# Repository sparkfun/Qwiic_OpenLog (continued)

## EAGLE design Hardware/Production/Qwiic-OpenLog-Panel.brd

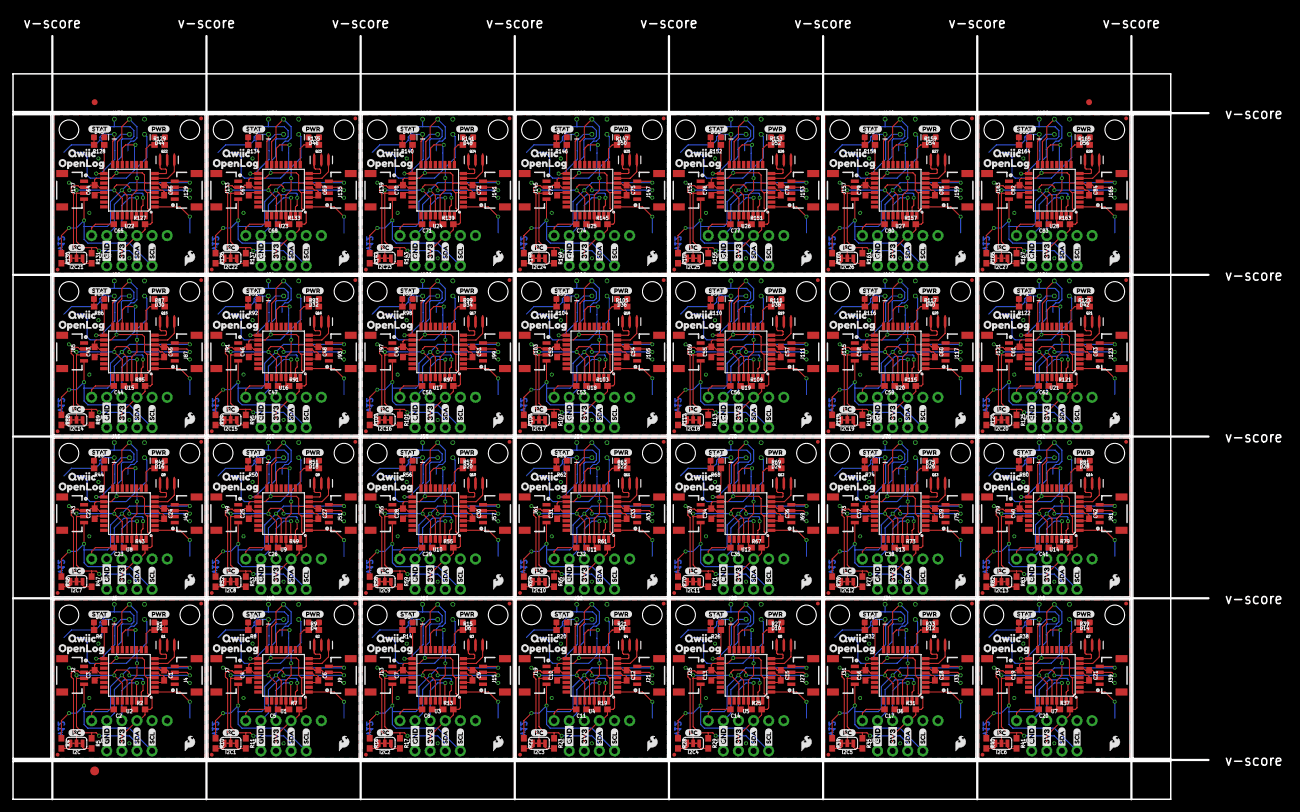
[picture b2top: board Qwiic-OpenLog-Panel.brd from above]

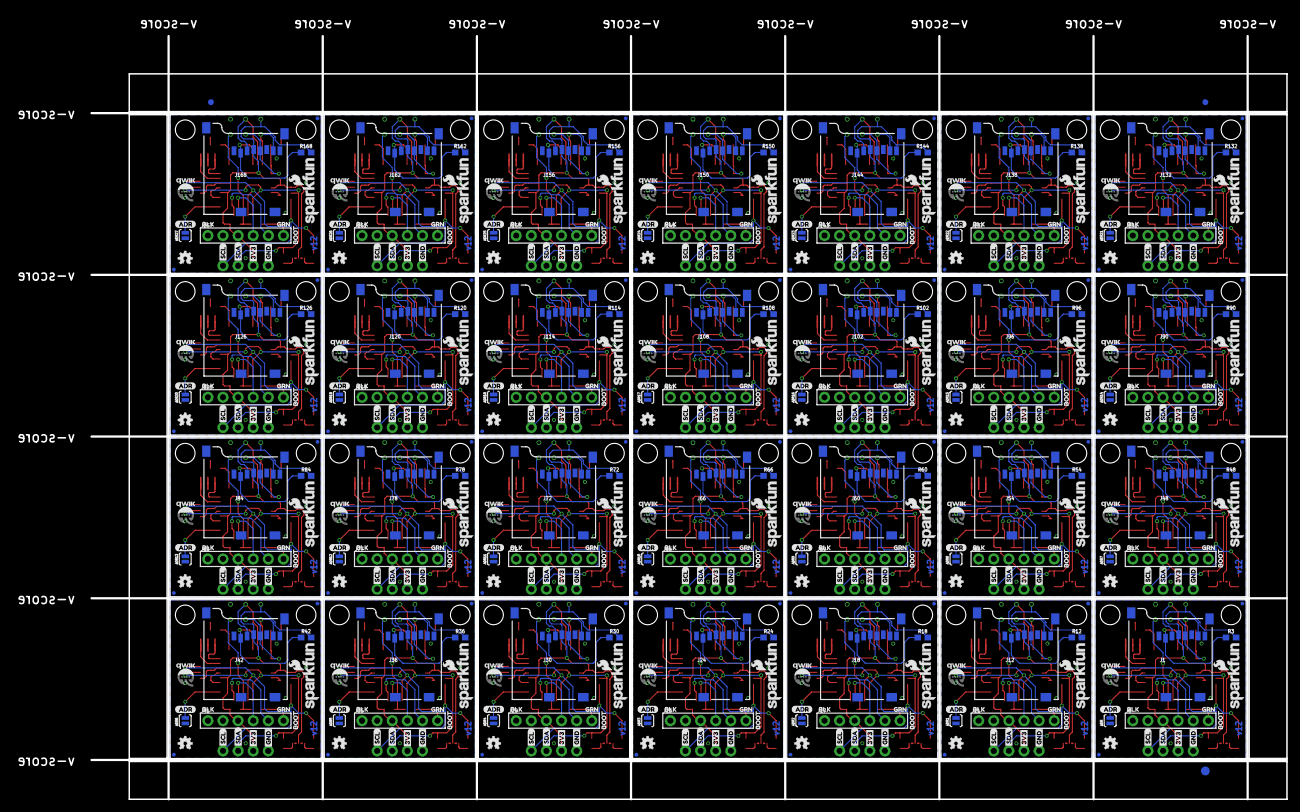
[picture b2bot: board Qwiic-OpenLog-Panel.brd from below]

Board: 2 copper layers, 200.9 x 128.3 mm, 1350 parts (479 on the bottom side), 560 nets.

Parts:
ADR, ADR1, ADR2, ADR3, ADR4, ADR5, ADR6, ADR7, ADR8, ADR9, ADR10, ADR11, ADR12, ADR13, ADR14, ADR15, ADR16, ADR17, ADR18, ADR19, ADR20, ADR21, ADR22, ADR23, ADR24, ADR25, ADR26, ADR27: SJ_2S-NO
C1, C6, C9, C12, C15, C18, C21, C24, C27, C30, C33, C36, C39, C42, C45, C48, C51, C54, C57, C60, C63, C66, C69, C72, C75, C78, C81, C84: 4.7uF; 0603
C2, C3, C4, C5, C7, C8, C10, C11, C13, C14, C16, C17, C19, C20, C22, C23, C25, C26, C28, C29, C31, C32, C34, C35, C37, C38, C40, C41, C43, C44, C46, C47, C49, C50, C52, C53, C55, C56, C58, C59, C61, C62, C64, C65, C67, C68, C70, C71, C73, C74, C76, C77, C79, C80, C82, C83: 0.1uF; 0603
D1, D4, D6, D8, D10, D12, D14, D16, D18, D20, D22, D24, D26, D28, D30, D32, D34, D36, D38, D40, D42, D44, D46, D48, D50, D52, D54, D56: RED; LED-0603
D2, D3, D5, D7, D9, D11, D13, D15, D17, D19, D21, D23, D25, D27, D29, D31, D33, D35, D37, D39, D41, D43, D45, D47, D49, D51, D53, D55: GREEN; LED-0603
E$1, E$2, E$3, E$4: FIDUCIAL-1X2
E$5, E$6: FIDUCIAL-1.5X3
FID1, FID2, FID3, FID4, FID5, FID6, FID7, FID8, FID9, FID10, FID11, FID12, FID13, FID14, FID15, FID16, FID17, FID18, FID19, FID20, FID21, FID22, FID23, FID24, FID25, FID26, FID27, FID28, FID29, FID30, FID31, FID32, FID33, FID34, FID35, FID36, FID37, FID38, FID39, FID40, FID41, FID42, FID43, FID44, FID45, FID46, FID47, FID48, FID49, FID50, FID51, FID52, FID53, FID54, FID55, FID56, FID57, FID58, FID59, FID60, FID61, FID62, FID63, FID64, FID65, FID66, FID67, FID68, FID69, FID70, FID71, FID72, FID73, FID74, FID75, FID76, FID77, FID78, FID79, FID80, FID81, FID82, FID83, FID84, FID85, FID86, FID87, FID88, FID89, FID90, FID91, FID92, FID93, FID94, FID95, FID96, FID97, FID98, FID99, FID100, FID101, FID102, FID103, FID104, FID105, FID106, FID107, FID108, FID109, FID110, FID111, FID112: FIDUCIALUFIDUCIAL; FIDUCIAL-MICRO
I2C, I2C1, I2C2, I2C3, I2C4, I2C5, I2C6, I2C7, I2C8, I2C9, I2C10, I2C11, I2C12, I2C13, I2C14, I2C15, I2C16, I2C17, I2C18, I2C19, I2C20, I2C21, I2C22, I2C23, I2C24, I2C25, I2C26, I2C27: SMT-JUMPER_3_2-NC_TRACE_SILK
J1, J12, J18, J24, J30, J36, J42, J48, J54, J60, J66, J72, J78, J84, J90, J96, J102, J108, J114, J120, J126, J132, J138, J144, J150, J156, J162, J168: MICRO-SD; MICRO-SD-SOCKET
J2, J4, J7, J9, J13, J15, J19, J21, J25, J27, J31, J33, J37, J39, J43, J45, J49, J51, J55, J57, J61, J63, J67, J69, J73, J75, J79, J81, J85, J87, J91, J93, J97, J99, J103, J105, J109, J111, J115, J117, J121, J123, J127, J129, J133, J135, J139, J141, J145, J147, J151, J153, J157, J159, J163, J165: SMD; 1X04_1MM_RA
J3, J8, J14, J20, J26, J32, J38, J44, J50, J56, J62, J68, J74, J80, J86, J92, J98, J104, J110, J116, J122, J128, J134, J140, J146, J152, J158, J164: PTH; 1X04_NO_SILK
J5, J10, J16, J22, J28, J34, J40, J46, J52, J58, J64, J70, J76, J82, J88, J94, J100, J106, J112, J118, J124, J130, J136, J142, J148, J154, J160, J166: ISP; 2X3_TEST_POINTS
J6, J11, J17, J23, J29, J35, J41, J47, J53, J59, J65, J71, J77, J83, J89, J95, J101, J107, J113, J119, J125, J131, J137, J143, J149, J155, J161, J167: 1X06_NO_SILK
JP1, JP2, JP3, JP4, JP5, JP6, JP7, JP8, JP9, JP10, JP11, JP12, JP13, JP14, JP15, JP16, JP17, JP18, JP19, JP20, JP21, JP22, JP23, JP24, JP25, JP26, JP27, JP28, JP29, JP30, JP31, JP32, JP33, JP34, JP35, JP36, JP37, JP38, JP39, JP40, JP41, JP42, JP43, JP44, JP45, JP46, JP47, JP48, JP49, JP50, JP51, JP52, JP53, JP54, JP55, JP56: STAND-OFF
LOGO1, LOGO6, LOGO9, LOGO12, LOGO15, LOGO18, LOGO21, LOGO24, LOGO27, LOGO30, LOGO33, LOGO36, LOGO39, LOGO42, LOGO45, LOGO48, LOGO51, LOGO54, LOGO57, LOGO60, LOGO63, LOGO66, LOGO69, LOGO72, LOGO75, LOGO78, LOGO81, LOGO84: SFE_LOGO_FLAME.1_INCH; SFE_LOGO_FLAME_.1
LOGO2, LOGO3, LOGO7, LOGO10, LOGO13, LOGO16, LOGO19, LOGO22, LOGO25, LOGO28, LOGO31, LOGO34, LOGO37, LOGO40, LOGO43, LOGO46, LOGO49, LOGO52, LOGO55, LOGO58, LOGO61, LOGO64, LOGO67, LOGO70, LOGO73, LOGO76, LOGO79, LOGO82: OSHW-LOGOMINI; OSHW-LOGO-MINI
LOGO4, LOGO5, LOGO8, LOGO11, LOGO14, LOGO17, LOGO20, LOGO23, LOGO26, LOGO29, LOGO32, LOGO35, LOGO38, LOGO41, LOGO44, LOGO47, LOGO50, LOGO53, LOGO56, LOGO59, LOGO62, LOGO65, LOGO68, LOGO71, LOGO74, LOGO77, LOGO80, LOGO83: SFE_LOGO_NAME_FLAME.1_INCH; SFE_LOGO_NAME_FLAME_.1
Q1, Q2, Q3, Q4, Q5, Q6, Q7, Q8, Q9, Q10, Q11, Q12, Q13, Q14, Q15, Q16, Q17, Q18, Q19, Q20, Q21, Q22, Q23, Q24, Q25, Q26, Q27, Q28: 16MHZ; RESONATOR-SMD
R1, R9, R15, R21, R27, R33, R39, R45, R51, R57, R63, R69, R75, R81, R87, R93, R99, R105, R111, R117, R123, R129, R135, R141, R147, R153, R159, R165: 1k; 0603
R2, R3, R7, R12, R13, R18, R19, R24, R25, R30, R31, R36, R37, R42, R43, R48, R49, R54, R55, R60, R61, R66, R67, R72, R73, R78, R79, R84, R85, R90, R91, R96, R97, R102, R103, R108, R109, R114, R115, R120, R121, R126, R127, R132, R133, R138, R139, R144, R145, R150, R151, R156, R157, R162, R163, R168: 10k; 0603
R4, R5, R10, R11, R16, R17, R22, R23, R28, R29, R34, R35, R40, R41, R46, R47, R52, R53, R58, R59, R64, R65, R70, R71, R76, R77, R82, R83, R88, R89, R94, R95, R100, R101, R106, R107, R112, R113, R118, R119, R124, R125, R130, R131, R136, R137, R142, R143, R148, R149, R154, R155, R160, R161, R166, R167: 2.2k; 0603
R6, R8, R14, R20, R26, R32, R38, R44, R50, R56, R62, R68, R74, R80, R86, R92, R98, R104, R110, R116, R122, R128, R134, R140, R146, R152, R158, R164: 330; 0603
U1, U2, U3, U4, U5, U6, U7, U8, U9, U10, U11, U12, U13, U14, U15, U16, U17, U18, U19, U20, U21, U22, U23, U24, U25, U26, U27, U28: ATMEGA328P; TQFP32-08
U$1, U$4, U$37, U$55, U$73, U$91, U$109, U$127, U$145, U$163, U$181, U$199, U$217, U$235, U$253, U$271, U$289, U$307, U$325, U$343, U$361, U$379, U$397, U$415, U$433, U$451, U$469, U$487: 3V3-03
U$2, U$5, U$38, U$56, U$74, U$92, U$110, U$128, U$146, U$164, U$182, U$200, U$218, U$236, U$254, U$272, U$290, U$308, U$326, U$344, U$362, U$380, U$398, U$416, U$434, U$452, U$470, U$488: GND-03
U$3, U$36, U$54, U$72, U$90, U$108, U$126, U$144, U$162, U$180, U$198, U$216, U$234, U$252, U$270, U$288, U$306, U$324, U$342, U$360, U$378, U$396, U$414, U$432, U$450, U$468, U$486, U$504: QWIIC-LOGO-SMALL
U$6, U$34, U$52, U$70, U$88, U$106, U$124, U$142, U$160, U$178, U$196, U$214, U$232, U$250, U$268, U$286, U$304, U$322, U$340, U$358, U$376, U$394, U$412, U$430, U$448, U$466, U$484, U$502: 3V30
U$7, U$21, U$39, U$57, U$75, U$93, U$111, U$129, U$147, U$165, U$183, U$201, U$219, U$237, U$255, U$273, U$291, U$309, U$327, U$345, U$363, U$381, U$399, U$417, U$435, U$453, U$471, U$489: ADR-()-03
U$8, U$22, U$40, U$58, U$76, U$94, U$112, U$130, U$148, U$166, U$184, U$202, U$220, U$238, U$256, U$274, U$292, U$310, U$328, U$346, U$364, U$382, U$400, U$418, U$436, U$454, U$472, U$490: I_SUPER2_C-()-03
U$9, U$23, U$41, U$59, U$77, U$95, U$113, U$131, U$149, U$167, U$185, U$203, U$221, U$239, U$257, U$275, U$293, U$311, U$329, U$347, U$365, U$383, U$401, U$419, U$437, U$455, U$473, U$491: PWR-()-03
U$10, U$24, U$42, U$60, U$78, U$96, U$114, U$132, U$150, U$168, U$186, U$204, U$222, U$240, U$258, U$276, U$294, U$312, U$330, U$348, U$366, U$384, U$402, U$420, U$438, U$456, U$474, U$492: BLK3
U$11, U$25, U$43, U$61, U$79, U$97, U$115, U$133, U$151, U$169, U$187, U$205, U$223, U$241, U$259, U$277, U$295, U$313, U$331, U$349, U$367, U$385, U$403, U$421, U$439, U$457, U$475, U$493: BOOT5
U$12, U$26, U$44, U$62, U$80, U$98, U$116, U$134, U$152, U$170, U$188, U$206, U$224, U$242, U$260, U$278, U$296, U$314, U$332, U$350, U$368, U$386, U$404, U$422, U$440, U$458, U$476, U$494: GRN4
U$13, U$16, U$29, U$32, U$47, U$50, U$65, U$68, U$83, U$86, U$101, U$104, U$119, U$122, U$137, U$140, U$155, U$158, U$173, U$176, U$191, U$194, U$209, U$212, U$227, U$230, U$245, U$248, U$263, U$266, U$281, U$284, U$299, U$302, U$317, U$320, U$335, U$338, U$353, U$356, U$371, U$374, U$389, U$392, U$407, U$410, U$425, U$428, U$443, U$446, U$461, U$464, U$479, U$482, U$497, U$500: SDA1
U$14, U$27, U$45, U$63, U$81, U$99, U$117, U$135, U$153, U$171, U$189, U$207, U$225, U$243, U$261, U$279, U$297, U$315, U$333, U$351, U$369, U$387, U$405, U$423, U$441, U$459, U$477, U$495: QWIIC7
U$15, U$19, U$28, U$33, U$46, U$51, U$64, U$69, U$82, U$87, U$100, U$105, U$118, U$123, U$136, U$141, U$154, U$159, U$172, U$177, U$190, U$195, U$208, U$213, U$226, U$231, U$244, U$249, U$262, U$267, U$280, U$285, U$298, U$303, U$316, U$321, U$334, U$339, U$352, U$357, U$370, U$375, U$388, U$393, U$406, U$411, U$424, U$429, U$442, U$447, U$460, U$465, U$478, U$483, U$496, U$501: SCL2
U$17, U$30, U$48, U$66, U$84, U$102, U$120, U$138, U$156, U$174, U$192, U$210, U$228, U$246, U$264, U$282, U$300, U$318, U$336, U$354, U$372, U$390, U$408, U$426, U$444, U$462, U$480, U$498: STAT0
U$18, U$31, U$49, U$67, U$85, U$103, U$121, U$139, U$157, U$175, U$193, U$211, U$229, U$247, U$265, U$283, U$301, U$319, U$337, U$355, U$373, U$391, U$409, U$427, U$445, U$463, U$481, U$499: OPENLOG0
U$20, U$35, U$53, U$71, U$89, U$107, U$125, U$143, U$161, U$179, U$197, U$215, U$233, U$251, U$269, U$287, U$305, U$323, U$341, U$359, U$377, U$395, U$413, U$431, U$449, U$467, U$485, U$503: GND1

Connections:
3.3V: C1.1, C3.2, I2C.2, J1.VCC, J2.2, J3.2, J4.2, J5.2, J6.3, R2.2, R3.2, U2.4, U2.6, U2.18, U2.20
3.3V1: C4.2, C6.1, I2C1.2, J7.2, J8.2, J9.2, J10.2, J11.3, J12.VCC, R7.2, R12.2, U1.4, U1.6, U1.18, U1.20
3.3V2: C7.2, C9.1, I2C2.2, J13.2, J14.2, J15.2, J16.2, J17.3, J18.VCC, R13.2, R18.2, U3.4, U3.6, U3.18, U3.20
3.3V3: C10.2, C12.1, I2C3.2, J19.2, J20.2, J21.2, J22.2, J23.3, J24.VCC, R19.2, R24.2, U4.4, U4.6, U4.18, U4.20
3.3V4: C13.2, C15.1, I2C4.2, J25.2, J26.2, J27.2, J28.2, J29.3, J30.VCC, R25.2, R30.2, U5.4, U5.6, U5.18, U5.20
3.3V5: C16.2, C18.1, I2C5.2, J31.2, J32.2, J33.2, J34.2, J35.3, J36.VCC, R31.2, R36.2, U6.4, U6.6, U6.18, U6.20
3.3V6: C19.2, C21.1, I2C6.2, J37.2, J38.2, J39.2, J40.2, J41.3, J42.VCC, R37.2, R42.2, U7.4, U7.6, U7.18, U7.20
3.3V7: C22.2, C24.1, I2C7.2, J43.2, J44.2, J45.2, J46.2, J47.3, J48.VCC, R43.2, R48.2, U8.4, U8.6, U8.18, U8.20
3.3V8: C25.2, C27.1, I2C8.2, J49.2, J50.2, J51.2, J52.2, J53.3, J54.VCC, R49.2, R54.2, U9.4, U9.6, U9.18, U9.20
3.3V9: C28.2, C30.1, I2C9.2, J55.2, J56.2, J57.2, J58.2, J59.3, J60.VCC, R55.2, R60.2, U10.4, U10.6, U10.18, U10.20
3.3V10: C31.2, C33.1, I2C10.2, J61.2, J62.2, J63.2, J64.2, J65.3, J66.VCC, R61.2, R66.2, U11.4, U11.6, U11.18, U11.20
3.3V11: C34.2, C36.1, I2C11.2, J67.2, J68.2, J69.2, J70.2, J71.3, J72.VCC, R67.2, R72.2, U12.4, U12.6, U12.18, U12.20
3.3V12: C37.2, C39.1, I2C12.2, J73.2, J74.2, J75.2, J76.2, J77.3, J78.VCC, R73.2, R78.2, U13.4, U13.6, U13.18, U13.20
3.3V13: C40.2, C42.1, I2C13.2, J79.2, J80.2, J81.2, J82.2, J83.3, J84.VCC, R79.2, R84.2, U14.4, U14.6, U14.18, U14.20
3.3V14: C43.2, C45.1, I2C14.2, J85.2, J86.2, J87.2, J88.2, J89.3, J90.VCC, R85.2, R90.2, U15.4, U15.6, U15.18, U15.20
3.3V15: C46.2, C48.1, I2C15.2, J91.2, J92.2, J93.2, J94.2, J95.3, J96.VCC, R91.2, R96.2, U16.4, U16.6, U16.18, U16.20
3.3V16: C49.2, C51.1, I2C16.2, J97.2, J98.2, J99.2, J100.2, J101.3, J102.VCC, R97.2, R102.2, U17.4, U17.6, U17.18, U17.20
3.3V17: C52.2, C54.1, I2C17.2, J103.2, J104.2, J105.2, J106.2, J107.3, J108.VCC, R103.2, R108.2, U18.4, U18.6, U18.18, U18.20
3.3V18: C55.2, C57.1, I2C18.2, J109.2, J110.2, J111.2, J112.2, J113.3, J114.VCC, R109.2, R114.2, U19.4, U19.6, U19.18, U19.20
3.3V19: C58.2, C60.1, I2C19.2, J115.2, J116.2, J117.2, J118.2, J119.3, J120.VCC, R115.2, R120.2, U20.4, U20.6, U20.18, U20.20
3.3V20: C61.2, C63.1, I2C20.2, J121.2, J122.2, J123.2, J124.2, J125.3, J126.VCC, R121.2, R126.2, U21.4, U21.6, U21.18, U21.20
3.3V21: C64.2, C66.1, I2C21.2, J127.2, J128.2, J129.2, J130.2, J131.3, J132.VCC, R127.2, R132.2, U22.4, U22.6, U22.18, U22.20
3.3V22: C67.2, C69.1, I2C22.2, J133.2, J134.2, J135.2, J136.2, J137.3, J138.VCC, R133.2, R138.2, U23.4, U23.6, U23.18, U23.20
3.3V23: C70.2, C72.1, I2C23.2, J139.2, J140.2, J141.2, J142.2, J143.3, J144.VCC, R139.2, R144.2, U24.4, U24.6, U24.18, U24.20
3.3V24: C73.2, C75.1, I2C24.2, J145.2, J146.2, J147.2, J148.2, J149.3, J150.VCC, R145.2, R150.2, U25.4, U25.6, U25.18, U25.20
3.3V25: C76.2, C78.1, I2C25.2, J151.2, J152.2, J153.2, J154.2, J155.3, J156.VCC, R151.2, R156.2, U26.4, U26.6, U26.18, U26.20
3.3V26: C79.2, C81.1, I2C26.2, J157.2, J158.2, J159.2, J160.2, J161.3, J162.VCC, R157.2, R162.2, U27.4, U27.6, U27.18, U27.20
3.3V27: C82.2, C84.1, I2C27.2, J163.2, J164.2, J165.2, J166.2, J167.3, J168.VCC, R163.2, R168.2, U28.4, U28.6, U28.18, U28.20
ADDR: ADR.2, U2.1
ADDR1: ADR1.2, U1.1
ADDR2: ADR2.2, U3.1
ADDR3: ADR3.2, U4.1
ADDR4: ADR4.2, U5.1
ADDR5: ADR5.2, U6.1
ADDR6: ADR6.2, U7.1
ADDR7: ADR7.2, U8.1
ADDR8: ADR8.2, U9.1
ADDR9: ADR9.2, U10.1
ADDR10: ADR10.2, U11.1
ADDR11: ADR11.2, U12.1
ADDR12: ADR12.2, U13.1
ADDR13: ADR13.2, U14.1
ADDR14: ADR14.2, U15.1
ADDR15: ADR15.2, U16.1
ADDR16: ADR16.2, U17.1
ADDR17: ADR17.2, U18.1
ADDR18: ADR18.2, U19.1
ADDR19: ADR19.2, U20.1
ADDR20: ADR20.2, U21.1
ADDR21: ADR21.2, U22.1
ADDR22: ADR22.2, U23.1
ADDR23: ADR23.2, U24.1
ADDR24: ADR24.2, U25.1
ADDR25: ADR25.2, U26.1
ADDR26: ADR26.2, U27.1
ADDR27: ADR27.2, U28.1
CS: J1.CS, R3.1, U2.14
CS1: J12.CS, R12.1, U1.14
CS2: J18.CS, R18.1, U3.14
CS3: J24.CS, R24.1, U4.14
CS4: J30.CS, R30.1, U5.14
CS5: J36.CS, R36.1, U6.14
CS6: J42.CS, R42.1, U7.14
CS7: J48.CS, R48.1, U8.14
CS8: J54.CS, R54.1, U9.14
CS9: J60.CS, R60.1, U10.14
CS10: J66.CS, R66.1, U11.14
CS11: J72.CS, R72.1, U12.14
CS12: J78.CS, R78.1, U13.14
CS13: J84.CS, R84.1, U14.14
CS14: J90.CS, R90.1, U15.14
CS15: J96.CS, R96.1, U16.14
CS16: J102.CS, R102.1, U17.14
CS17: J108.CS, R108.1, U18.14
CS18: J114.CS, R114.1, U19.14
CS19: J120.CS, R120.1, U20.14
CS20: J126.CS, R126.1, U21.14
CS21: J132.CS, R132.1, U22.14
CS22: J138.CS, R138.1, U23.14
CS23: J144.CS, R144.1, U24.14
CS24: J150.CS, R150.1, U25.14
CS25: J156.CS, R156.1, U26.14
CS26: J162.CS, R162.1, U27.14
CS27: J168.CS, R168.1, U28.14
DTR: C2.2, J6.6
DTR1: C5.2, J11.6
DTR2: C8.2, J17.6
DTR3: C11.2, J23.6
DTR4: C14.2, J29.6
DTR5: C17.2, J35.6
DTR6: C20.2, J41.6
DTR7: C23.2, J47.6
DTR8: C26.2, J53.6
DTR9: C29.2, J59.6
DTR10: C32.2, J65.6
DTR11: C35.2, J71.6
DTR12: C38.2, J77.6
DTR13: C41.2, J83.6
DTR14: C44.2, J89.6
DTR15: C47.2, J95.6
DTR16: C50.2, J101.6
DTR17: C53.2, J107.6
DTR18: C56.2, J113.6
DTR19: C59.2, J119.6
DTR20: C62.2, J125.6
DTR21: C65.2, J131.6
DTR22: C68.2, J137.6
DTR23: C71.2, J143.6
DTR24: C74.2, J149.6
DTR25: C77.2, J155.6
DTR26: C80.2, J161.6
DTR27: C83.2, J167.6
GND: ADR.1, C1.2, C3.1, D1.C, D3.C, J1.GND, J2.1, J3.1, J4.1, J5.6, J6.1, J6.2, Q1.2, U2.3, U2.5, U2.21
GND1: ADR1.1, C4.1, C6.2, D2.C, D4.C, J7.1, J8.1, J9.1, J10.6, J11.1, J11.2, J12.GND, Q2.2, U1.3, U1.5, U1.21
GND2: ADR2.1, C7.1, C9.2, D5.C, D6.C, J13.1, J14.1, J15.1, J16.6, J17.1, J17.2, J18.GND, Q3.2, U3.3, U3.5, U3.21
GND3: ADR3.1, C10.1, C12.2, D7.C, D8.C, J19.1, J20.1, J21.1, J22.6, J23.1, J23.2, J24.GND, Q4.2, U4.3, U4.5, U4.21
GND4: ADR4.1, C13.1, C15.2, D9.C, D10.C, J25.1, J26.1, J27.1, J28.6, J29.1, J29.2, J30.GND, Q5.2, U5.3, U5.5, U5.21
GND5: ADR5.1, C16.1, C18.2, D11.C, D12.C, J31.1, J32.1, J33.1, J34.6, J35.1, J35.2, J36.GND, Q6.2, U6.3, U6.5, U6.21
GND6: ADR6.1, C19.1, C21.2, D13.C, D14.C, J37.1, J38.1, J39.1, J40.6, J41.1, J41.2, J42.GND, Q7.2, U7.3, U7.5, U7.21
GND7: ADR7.1, C22.1, C24.2, D15.C, D16.C, J43.1, J44.1, J45.1, J46.6, J47.1, J47.2, J48.GND, Q8.2, U8.3, U8.5, U8.21
GND8: ADR8.1, C25.1, C27.2, D17.C, D18.C, J49.1, J50.1, J51.1, J52.6, J53.1, J53.2, J54.GND, Q9.2, U9.3, U9.5, U9.21
GND9: ADR9.1, C28.1, C30.2, D19.C, D20.C, J55.1, J56.1, J57.1, J58.6, J59.1, J59.2, J60.GND, Q10.2, U10.3, U10.5, U10.21
GND10: ADR10.1, C31.1, C33.2, D21.C, D22.C, J61.1, J62.1, J63.1, J64.6, J65.1, J65.2, J66.GND, Q11.2, U11.3, U11.5, U11.21
GND11: ADR11.1, C34.1, C36.2, D23.C, D24.C, J67.1, J68.1, J69.1, J70.6, J71.1, J71.2, J72.GND, Q12.2, U12.3, U12.5, U12.21
GND12: ADR12.1, C37.1, C39.2, D25.C, D26.C, J73.1, J74.1, J75.1, J76.6, J77.1, J77.2, J78.GND, Q13.2, U13.3, U13.5, U13.21
GND13: ADR13.1, C40.1, C42.2, D27.C, D28.C, J79.1, J80.1, J81.1, J82.6, J83.1, J83.2, J84.GND, Q14.2, U14.3, U14.5, U14.21
GND14: ADR14.1, C43.1, C45.2, D29.C, D30.C, J85.1, J86.1, J87.1, J88.6, J89.1, J89.2, J90.GND, Q15.2, U15.3, U15.5, U15.21
GND15: ADR15.1, C46.1, C48.2, D31.C, D32.C, J91.1, J92.1, J93.1, J94.6, J95.1, J95.2, J96.GND, Q16.2, U16.3, U16.5, U16.21
GND16: ADR16.1, C49.1, C51.2, D33.C, D34.C, J97.1, J98.1, J99.1, J100.6, J101.1, J101.2, J102.GND, Q17.2, U17.3, U17.5, U17.21
GND17: ADR17.1, C52.1, C54.2, D35.C, D36.C, J103.1, J104.1, J105.1, J106.6, J107.1, J107.2, J108.GND, Q18.2, U18.3, U18.5, U18.21
GND18: ADR18.1, C55.1, C57.2, D37.C, D38.C, J109.1, J110.1, J111.1, J112.6, J113.1, J113.2, J114.GND, Q19.2, U19.3, U19.5, U19.21
GND19: ADR19.1, C58.1, C60.2, D39.C, D40.C, J115.1, J116.1, J117.1, J118.6, J119.1, J119.2, J120.GND, Q20.2, U20.3, U20.5, U20.21
GND20: ADR20.1, C61.1, C63.2, D41.C, D42.C, J121.1, J122.1, J123.1, J124.6, J125.1, J125.2, J126.GND, Q21.2, U21.3, U21.5, U21.21
GND21: ADR21.1, C64.1, C66.2, D43.C, D44.C, J127.1, J128.1, J129.1, J130.6, J131.1, J131.2, J132.GND, Q22.2, U22.3, U22.5, U22.21
GND22: ADR22.1, C67.1, C69.2, D45.C, D46.C, J133.1, J134.1, J135.1, J136.6, J137.1, J137.2, J138.GND, Q23.2, U23.3, U23.5, U23.21
GND23: ADR23.1, C70.1, C72.2, D47.C, D48.C, J139.1, J140.1, J141.1, J142.6, J143.1, J143.2, J144.GND, Q24.2, U24.3, U24.5, U24.21
GND24: ADR24.1, C73.1, C75.2, D49.C, D50.C, J145.1, J146.1, J147.1, J148.6, J149.1, J149.2, J150.GND, Q25.2, U25.3, U25.5, U25.21
GND25: ADR25.1, C76.1, C78.2, D51.C, D52.C, J151.1, J152.1, J153.1, J154.6, J155.1, J155.2, J156.GND, Q26.2, U26.3, U26.5, U26.21
GND26: ADR26.1, C79.1, C81.2, D53.C, D54.C, J157.1, J158.1, J159.1, J160.6, J161.1, J161.2, J162.GND, Q27.2, U27.3, U27.5, U27.21
GND27: ADR27.1, C82.1, C84.2, D55.C, D56.C, J163.1, J164.1, J165.1, J166.6, J167.1, J167.2, J168.GND, Q28.2, U28.3, U28.5, U28.21
MISO: J1.DO, J5.1, U2.16
MISO1: J10.1, J12.DO, U1.16
MISO2: J16.1, J18.DO, U3.16
MISO3: J22.1, J24.DO, U4.16
MISO4: J28.1, J30.DO, U5.16
MISO5: J34.1, J36.DO, U6.16
MISO6: J40.1, J42.DO, U7.16
MISO7: J46.1, J48.DO, U8.16
MISO8: J52.1, J54.DO, U9.16
MISO9: J58.1, J60.DO, U10.16
MISO10: J64.1, J66.DO, U11.16
MISO11: J70.1, J72.DO, U12.16
MISO12: J76.1, J78.DO, U13.16
MISO13: J82.1, J84.DO, U14.16
MISO14: J88.1, J90.DO, U15.16
MISO15: J94.1, J96.DO, U16.16
MISO16: J100.1, J102.DO, U17.16
MISO17: J106.1, J108.DO, U18.16
MISO18: J112.1, J114.DO, U19.16
MISO19: J118.1, J120.DO, U20.16
MISO20: J124.1, J126.DO, U21.16
MISO21: J130.1, J132.DO, U22.16
MISO22: J136.1, J138.DO, U23.16
MISO23: J142.1, J144.DO, U24.16
MISO24: J148.1, J150.DO, U25.16
MISO25: J154.1, J156.DO, U26.16
MISO26: J160.1, J162.DO, U27.16
MISO27: J166.1, J168.DO, U28.16
MOSI: J1.DI, J5.4, U2.15
MOSI1: J10.4, J12.DI, U1.15
MOSI2: J16.4, J18.DI, U3.15
MOSI3: J22.4, J24.DI, U4.15
MOSI4: J28.4, J30.DI, U5.15
MOSI5: J34.4, J36.DI, U6.15
MOSI6: J40.4, J42.DI, U7.15
MOSI7: J46.4, J48.DI, U8.15
MOSI8: J52.4, J54.DI, U9.15
MOSI9: J58.4, J60.DI, U10.15
MOSI10: J64.4, J66.DI, U11.15
MOSI11: J70.4, J72.DI, U12.15
MOSI12: J76.4, J78.DI, U13.15
MOSI13: J82.4, J84.DI, U14.15
MOSI14: J88.4, J90.DI, U15.15
MOSI15: J94.4, J96.DI, U16.15
MOSI16: J100.4, J102.DI, U17.15
MOSI17: J106.4, J108.DI, U18.15
MOSI18: J112.4, J114.DI, U19.15
MOSI19: J118.4, J120.DI, U20.15
MOSI20: J124.4, J126.DI, U21.15
MOSI21: J130.4, J132.DI, U22.15
MOSI22: J136.4, J138.DI, U23.15
MOSI23: J142.4, J144.DI, U24.15
MOSI24: J148.4, J150.DI, U25.15
MOSI25: J154.4, J156.DI, U26.15
MOSI26: J160.4, J162.DI, U27.15
MOSI27: J166.4, J168.DI, U28.15
unnamed: Q1.1, U2.8
unnamed: Q1.3, U2.7
unnamed: D1.A, R1.2
unnamed: R1.1, U2.9
unnamed: I2C.1, R5.2
unnamed: I2C.3, R4.2
unnamed: D3.A, R6.2
unnamed: D2.A, R8.2
unnamed: Q2.1, U1.8
unnamed: Q2.3, U1.7
unnamed: D4.A, R9.2
unnamed: R9.1, U1.9
unnamed: I2C1.1, R11.2
unnamed: I2C1.3, R10.2
unnamed: D5.A, R14.2
unnamed: Q3.1, U3.8
unnamed: Q3.3, U3.7
unnamed: D6.A, R15.2
unnamed: R15.1, U3.9
unnamed: I2C2.1, R17.2
unnamed: I2C2.3, R16.2
unnamed: D7.A, R20.2
unnamed: Q4.1, U4.8
unnamed: Q4.3, U4.7
unnamed: D8.A, R21.2
unnamed: R21.1, U4.9
unnamed: I2C3.1, R23.2
unnamed: I2C3.3, R22.2
unnamed: D9.A, R26.2
unnamed: Q5.1, U5.8
unnamed: Q5.3, U5.7
unnamed: D10.A, R27.2
unnamed: R27.1, U5.9
unnamed: I2C4.1, R29.2
unnamed: I2C4.3, R28.2
unnamed: D11.A, R32.2
unnamed: Q6.1, U6.8
unnamed: Q6.3, U6.7
unnamed: D12.A, R33.2
unnamed: R33.1, U6.9
unnamed: I2C5.1, R35.2
unnamed: I2C5.3, R34.2
unnamed: D13.A, R38.2
unnamed: Q7.1, U7.8
unnamed: Q7.3, U7.7
unnamed: D14.A, R39.2
unnamed: R39.1, U7.9
unnamed: I2C6.1, R41.2
unnamed: I2C6.3, R40.2
unnamed: D15.A, R44.2
unnamed: Q8.1, U8.8
unnamed: Q8.3, U8.7
unnamed: D16.A, R45.2
unnamed: R45.1, U8.9
unnamed: I2C7.1, R47.2
unnamed: I2C7.3, R46.2
unnamed: D17.A, R50.2
unnamed: Q9.1, U9.8
unnamed: Q9.3, U9.7
unnamed: D18.A, R51.2
unnamed: R51.1, U9.9
unnamed: I2C8.1, R53.2
unnamed: I2C8.3, R52.2
unnamed: D19.A, R56.2
unnamed: Q10.1, U10.8
unnamed: Q10.3, U10.7
unnamed: D20.A, R57.2
unnamed: R57.1, U10.9
unnamed: I2C9.1, R59.2
unnamed: I2C9.3, R58.2
unnamed: D21.A, R62.2
unnamed: Q11.1, U11.8
unnamed: Q11.3, U11.7
unnamed: D22.A, R63.2
unnamed: R63.1, U11.9
unnamed: I2C10.1, R65.2
unnamed: I2C10.3, R64.2
unnamed: D23.A, R68.2
unnamed: Q12.1, U12.8
unnamed: Q12.3, U12.7
unnamed: D24.A, R69.2
unnamed: R69.1, U12.9
unnamed: I2C11.1, R71.2
unnamed: I2C11.3, R70.2
unnamed: D25.A, R74.2
unnamed: Q13.1, U13.8
unnamed: Q13.3, U13.7
unnamed: D26.A, R75.2
unnamed: R75.1, U13.9
unnamed: I2C12.1, R77.2
unnamed: I2C12.3, R76.2
unnamed: D27.A, R80.2
unnamed: Q14.1, U14.8
unnamed: Q14.3, U14.7
unnamed: D28.A, R81.2
unnamed: R81.1, U14.9
unnamed: I2C13.1, R83.2
unnamed: I2C13.3, R82.2
unnamed: D29.A, R86.2
unnamed: Q15.1, U15.8
unnamed: Q15.3, U15.7
unnamed: D30.A, R87.2
unnamed: R87.1, U15.9
unnamed: I2C14.1, R89.2
unnamed: I2C14.3, R88.2
unnamed: D31.A, R92.2
unnamed: Q16.1, U16.8
unnamed: Q16.3, U16.7
unnamed: D32.A, R93.2
unnamed: R93.1, U16.9
unnamed: I2C15.1, R95.2
unnamed: I2C15.3, R94.2
unnamed: D33.A, R98.2
unnamed: Q17.1, U17.8
unnamed: Q17.3, U17.7
unnamed: D34.A, R99.2
unnamed: R99.1, U17.9
unnamed: I2C16.1, R101.2
unnamed: I2C16.3, R100.2
unnamed: D35.A, R104.2
unnamed: Q18.1, U18.8
unnamed: Q18.3, U18.7
unnamed: D36.A, R105.2
unnamed: R105.1, U18.9
unnamed: I2C17.1, R107.2
unnamed: I2C17.3, R106.2
unnamed: D37.A, R110.2
unnamed: Q19.1, U19.8
unnamed: Q19.3, U19.7
unnamed: D38.A, R111.2
unnamed: R111.1, U19.9
unnamed: I2C18.1, R113.2
unnamed: I2C18.3, R112.2
unnamed: D39.A, R116.2
unnamed: Q20.1, U20.8
unnamed: Q20.3, U20.7
unnamed: D40.A, R117.2
unnamed: R117.1, U20.9
unnamed: I2C19.1, R119.2
unnamed: I2C19.3, R118.2
unnamed: D41.A, R122.2
unnamed: Q21.1, U21.8
unnamed: Q21.3, U21.7
unnamed: D42.A, R123.2
unnamed: R123.1, U21.9
unnamed: I2C20.1, R125.2
unnamed: I2C20.3, R124.2
unnamed: D43.A, R128.2
unnamed: Q22.1, U22.8
unnamed: Q22.3, U22.7
unnamed: D44.A, R129.2
unnamed: R129.1, U22.9
unnamed: I2C21.1, R131.2
unnamed: I2C21.3, R130.2
unnamed: D45.A, R134.2
unnamed: Q23.1, U23.8
unnamed: Q23.3, U23.7
unnamed: D46.A, R135.2
unnamed: R135.1, U23.9
unnamed: I2C22.1, R137.2
unnamed: I2C22.3, R136.2
unnamed: D47.A, R140.2
unnamed: Q24.1, U24.8
unnamed: Q24.3, U24.7
unnamed: D48.A, R141.2
unnamed: R141.1, U24.9
unnamed: I2C23.1, R143.2
unnamed: I2C23.3, R142.2
unnamed: D49.A, R146.2
unnamed: Q25.1, U25.8
unnamed: Q25.3, U25.7
unnamed: D50.A, R147.2
unnamed: R147.1, U25.9
unnamed: I2C24.1, R149.2
unnamed: I2C24.3, R148.2
unnamed: D51.A, R152.2
unnamed: Q26.1, U26.8
unnamed: Q26.3, U26.7
unnamed: D52.A, R153.2
unnamed: R153.1, U26.9
unnamed: I2C25.1, R155.2
unnamed: I2C25.3, R154.2
unnamed: D53.A, R158.2
unnamed: Q27.1, U27.8
unnamed: Q27.3, U27.7
unnamed: D54.A, R159.2
unnamed: R159.1, U27.9
unnamed: I2C26.1, R161.2
unnamed: I2C26.3, R160.2
unnamed: D55.A, R164.2
unnamed: Q28.1, U28.8
unnamed: Q28.3, U28.7
unnamed: D56.A, R165.2
unnamed: R165.1, U28.9
unnamed: I2C27.1, R167.2
unnamed: I2C27.3, R166.2
RST: C2.1, J5.5, R2.1, U2.29
RST1: C5.1, J10.5, R7.1, U1.29
RST2: C8.1, J16.5, R13.1, U3.29
RST3: C11.1, J22.5, R19.1, U4.29
RST4: C14.1, J28.5, R25.1, U5.29
RST5: C17.1, J34.5, R31.1, U6.29
RST6: C20.1, J40.5, R37.1, U7.29
RST7: C23.1, J46.5, R43.1, U8.29
RST8: C26.1, J52.5, R49.1, U9.29
RST9: C29.1, J58.5, R55.1, U10.29
RST10: C32.1, J64.5, R61.1, U11.29
RST11: C35.1, J70.5, R67.1, U12.29
RST12: C38.1, J76.5, R73.1, U13.29
RST13: C41.1, J82.5, R79.1, U14.29
RST14: C44.1, J88.5, R85.1, U15.29
RST15: C47.1, J94.5, R91.1, U16.29
RST16: C50.1, J100.5, R97.1, U17.29
RST17: C53.1, J106.5, R103.1, U18.29
RST18: C56.1, J112.5, R109.1, U19.29
RST19: C59.1, J118.5, R115.1, U20.29
RST20: C62.1, J124.5, R121.1, U21.29
RST21: C65.1, J130.5, R127.1, U22.29
RST22: C68.1, J136.5, R133.1, U23.29
RST23: C71.1, J142.5, R139.1, U24.29
RST24: C74.1, J148.5, R145.1, U25.29
RST25: C77.1, J154.5, R151.1, U26.29
RST26: C80.1, J160.5, R157.1, U27.29
RST27: C83.1, J166.5, R163.1, U28.29
RXI: J6.4, U2.30
RXI1: J11.4, U1.30
RXI2: J17.4, U3.30
RXI3: J23.4, U4.30
RXI4: J29.4, U5.30
RXI5: J35.4, U6.30
RXI6: J41.4, U7.30
RXI7: J47.4, U8.30
RXI8: J53.4, U9.30
RXI9: J59.4, U10.30
RXI10: J65.4, U11.30
RXI11: J71.4, U12.30
RXI12: J77.4, U13.30
RXI13: J83.4, U14.30
RXI14: J89.4, U15.30
RXI15: J95.4, U16.30
RXI16: J101.4, U17.30
RXI17: J107.4, U18.30
RXI18: J113.4, U19.30
RXI19: J119.4, U20.30
RXI20: J125.4, U21.30
RXI21: J131.4, U22.30
RXI22: J137.4, U23.30
RXI23: J143.4, U24.30
RXI24: J149.4, U25.30
RXI25: J155.4, U26.30
RXI26: J161.4, U27.30
RXI27: J167.4, U28.30
SCK: J1.SCLK, J5.3, R6.1, U2.17
SCK1: J10.3, J12.SCLK, R8.1, U1.17
SCK2: J16.3, J18.SCLK, R14.1, U3.17
SCK3: J22.3, J24.SCLK, R20.1, U4.17
SCK4: J28.3, J30.SCLK, R26.1, U5.17
SCK5: J34.3, J36.SCLK, R32.1, U6.17
SCK6: J40.3, J42.SCLK, R38.1, U7.17
SCK7: J46.3, J48.SCLK, R44.1, U8.17
SCK8: J52.3, J54.SCLK, R50.1, U9.17
SCK9: J58.3, J60.SCLK, R56.1, U10.17
SCK10: J64.3, J66.SCLK, R62.1, U11.17
SCK11: J70.3, J72.SCLK, R68.1, U12.17
SCK12: J76.3, J78.SCLK, R74.1, U13.17
SCK13: J82.3, J84.SCLK, R80.1, U14.17
SCK14: J88.3, J90.SCLK, R86.1, U15.17
SCK15: J94.3, J96.SCLK, R92.1, U16.17
SCK16: J100.3, J102.SCLK, R98.1, U17.17
SCK17: J106.3, J108.SCLK, R104.1, U18.17
SCK18: J112.3, J114.SCLK, R110.1, U19.17
SCK19: J118.3, J120.SCLK, R116.1, U20.17
SCK20: J124.3, J126.SCLK, R122.1, U21.17
SCK21: J130.3, J132.SCLK, R128.1, U22.17
SCK22: J136.3, J138.SCLK, R134.1, U23.17
SCK23: J142.3, J144.SCLK, R140.1, U24.17
SCK24: J148.3, J150.SCLK, R146.1, U25.17
SCK25: J154.3, J156.SCLK, R152.1, U26.17
SCK26: J160.3, J162.SCLK, R158.1, U27.17
SCK27: J166.3, J168.SCLK, R164.1, U28.17
SCL: J2.4, J3.4, J4.4, R4.1, U2.28
SCL1: J7.4, J8.4, J9.4, R10.1, U1.28
SCL2: J13.4, J14.4, J15.4, R16.1, U3.28
SCL3: J19.4, J20.4, J21.4, R22.1, U4.28
SCL4: J25.4, J26.4, J27.4, R28.1, U5.28
SCL5: J31.4, J32.4, J33.4, R34.1, U6.28
SCL6: J37.4, J38.4, J39.4, R40.1, U7.28
SCL7: J43.4, J44.4, J45.4, R46.1, U8.28
SCL8: J49.4, J50.4, J51.4, R52.1, U9.28
SCL9: J55.4, J56.4, J57.4, R58.1, U10.28
SCL10: J61.4, J62.4, J63.4, R64.1, U11.28
SCL11: J67.4, J68.4, J69.4, R70.1, U12.28
SCL12: J73.4, J74.4, J75.4, R76.1, U13.28
SCL13: J79.4, J80.4, J81.4, R82.1, U14.28
SCL14: J85.4, J86.4, J87.4, R88.1, U15.28
SCL15: J91.4, J92.4, J93.4, R94.1, U16.28
SCL16: J97.4, J98.4, J99.4, R100.1, U17.28
SCL17: J103.4, J104.4, J105.4, R106.1, U18.28
SCL18: J109.4, J110.4, J111.4, R112.1, U19.28
SCL19: J115.4, J116.4, J117.4, R118.1, U20.28
SCL20: J121.4, J122.4, J123.4, R124.1, U21.28
SCL21: J127.4, J128.4, J129.4, R130.1, U22.28
SCL22: J133.4, J134.4, J135.4, R136.1, U23.28
SCL23: J139.4, J140.4, J141.4, R142.1, U24.28
SCL24: J145.4, J146.4, J147.4, R148.1, U25.28
SCL25: J151.4, J152.4, J153.4, R154.1, U26.28
SCL26: J157.4, J158.4, J159.4, R160.1, U27.28
SCL27: J163.4, J164.4, J165.4, R166.1, U28.28
SDA: J2.3, J3.3, J4.3, R5.1, U2.27
SDA1: J7.3, J8.3, J9.3, R11.1, U1.27
SDA2: J13.3, J14.3, J15.3, R17.1, U3.27
SDA3: J19.3, J20.3, J21.3, R23.1, U4.27
SDA4: J25.3, J26.3, J27.3, R29.1, U5.27
SDA5: J31.3, J32.3, J33.3, R35.1, U6.27
SDA6: J37.3, J38.3, J39.3, R41.1, U7.27
SDA7: J43.3, J44.3, J45.3, R47.1, U8.27
SDA8: J49.3, J50.3, J51.3, R53.1, U9.27
SDA9: J55.3, J56.3, J57.3, R59.1, U10.27
SDA10: J61.3, J62.3, J63.3, R65.1, U11.27
SDA11: J67.3, J68.3, J69.3, R71.1, U12.27
SDA12: J73.3, J74.3, J75.3, R77.1, U13.27
SDA13: J79.3, J80.3, J81.3, R83.1, U14.27
SDA14: J85.3, J86.3, J87.3, R89.1, U15.27
SDA15: J91.3, J92.3, J93.3, R95.1, U16.27
SDA16: J97.3, J98.3, J99.3, R101.1, U17.27
SDA17: J103.3, J104.3, J105.3, R107.1, U18.27
SDA18: J109.3, J110.3, J111.3, R113.1, U19.27
SDA19: J115.3, J116.3, J117.3, R119.1, U20.27
SDA20: J121.3, J122.3, J123.3, R125.1, U21.27
SDA21: J127.3, J128.3, J129.3, R131.1, U22.27
SDA22: J133.3, J134.3, J135.3, R137.1, U23.27
SDA23: J139.3, J140.3, J141.3, R143.1, U24.27
SDA24: J145.3, J146.3, J147.3, R149.1, U25.27
SDA25: J151.3, J152.3, J153.3, R155.1, U26.27
SDA26: J157.3, J158.3, J159.3, R161.1, U27.27
SDA27: J163.3, J164.3, J165.3, R167.1, U28.27
TXO: J6.5, U2.31
TXO1: J11.5, U1.31
TXO2: J17.5, U3.31
TXO3: J23.5, U4.31
TXO4: J29.5, U5.31
TXO5: J35.5, U6.31
TXO6: J41.5, U7.31
TXO7: J47.5, U8.31
TXO8: J53.5, U9.31
TXO9: J59.5, U10.31
TXO10: J65.5, U11.31
TXO11: J71.5, U12.31
TXO12: J77.5, U13.31
TXO13: J83.5, U14.31
TXO14: J89.5, U15.31
TXO15: J95.5, U16.31
TXO16: J101.5, U17.31
TXO17: J107.5, U18.31
TXO18: J113.5, U19.31
TXO19: J119.5, U20.31
TXO20: J125.5, U21.31
TXO21: J131.5, U22.31
TXO22: J137.5, U23.31
TXO23: J143.5, U24.31
TXO24: J149.5, U25.31
TXO25: J155.5, U26.31
TXO26: J161.5, U27.31
TXO27: J167.5, U28.31
